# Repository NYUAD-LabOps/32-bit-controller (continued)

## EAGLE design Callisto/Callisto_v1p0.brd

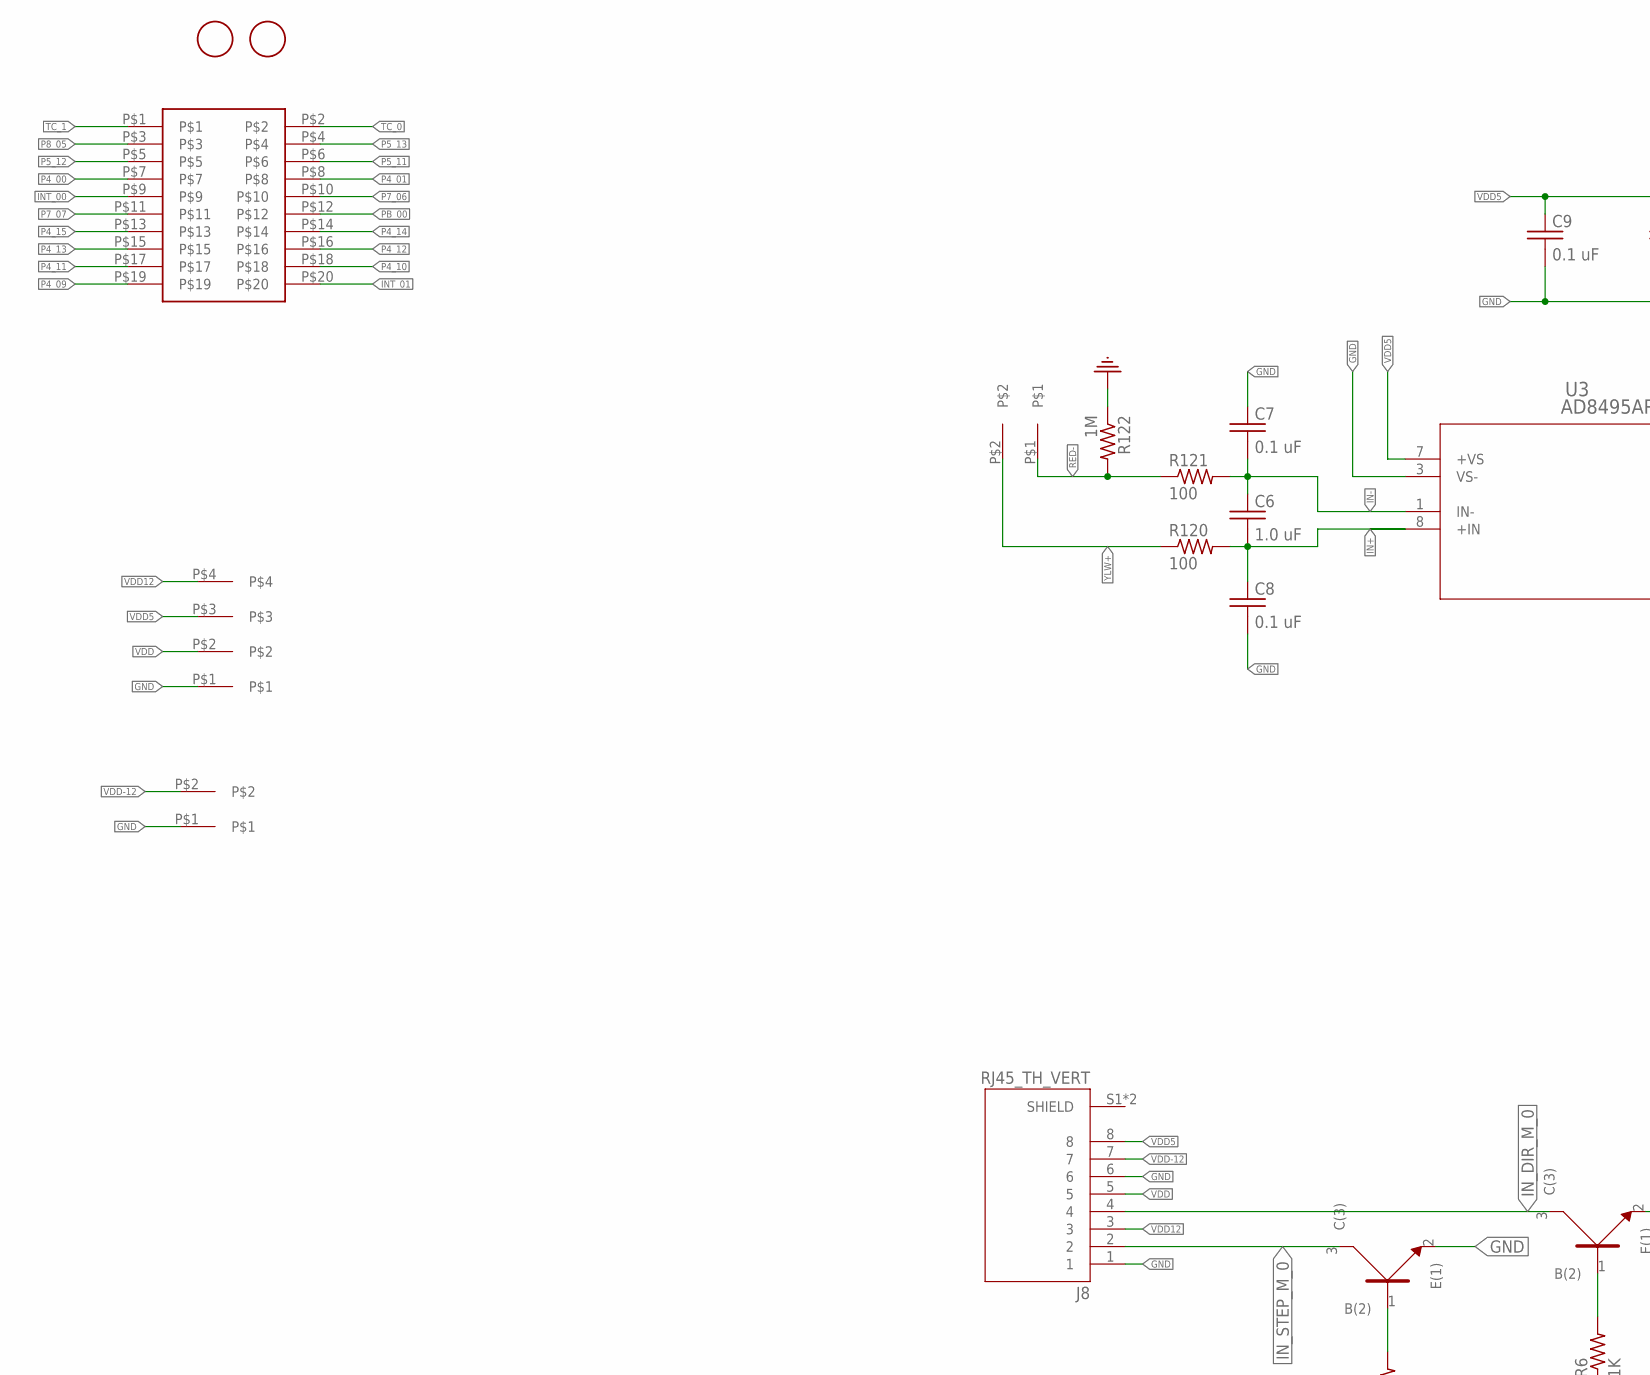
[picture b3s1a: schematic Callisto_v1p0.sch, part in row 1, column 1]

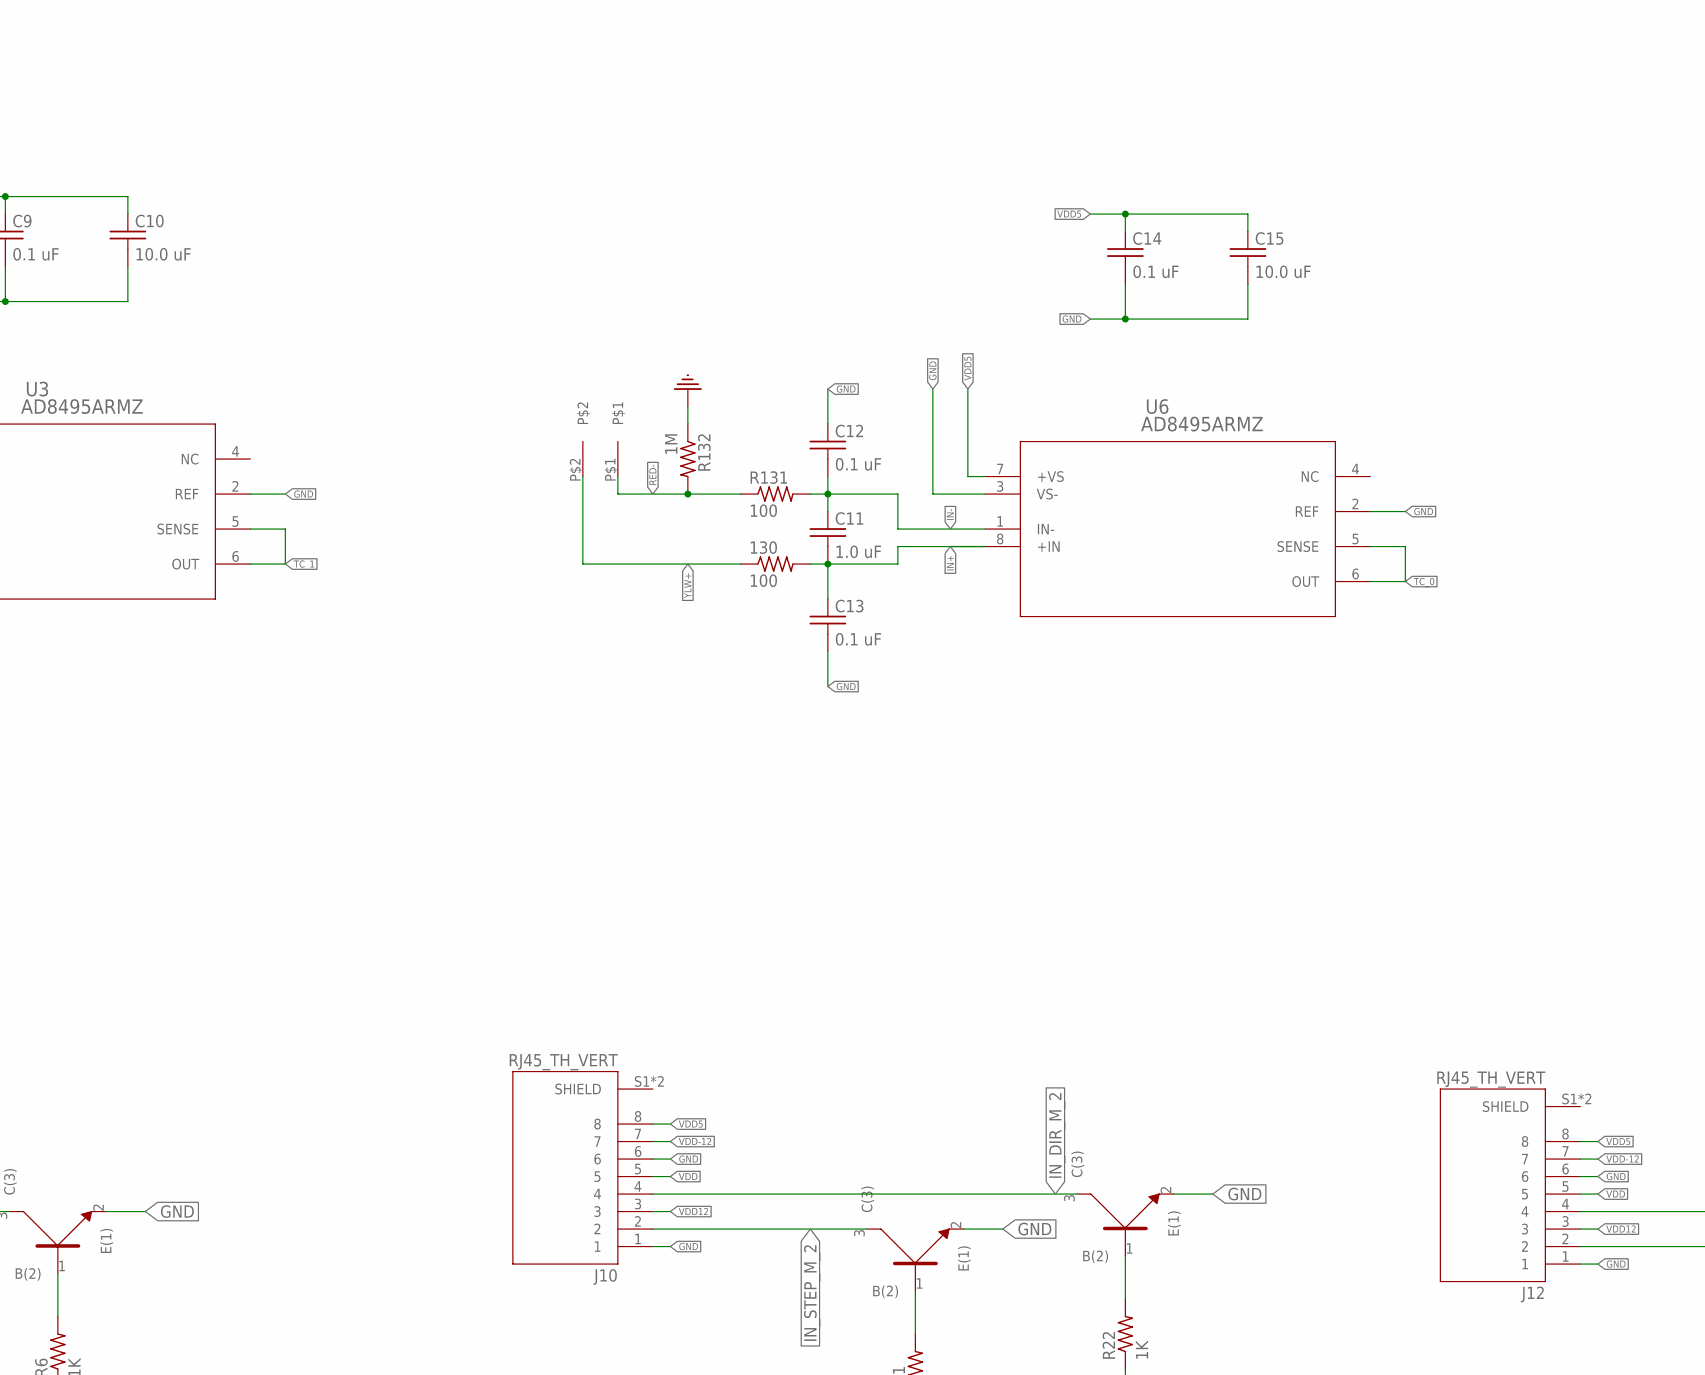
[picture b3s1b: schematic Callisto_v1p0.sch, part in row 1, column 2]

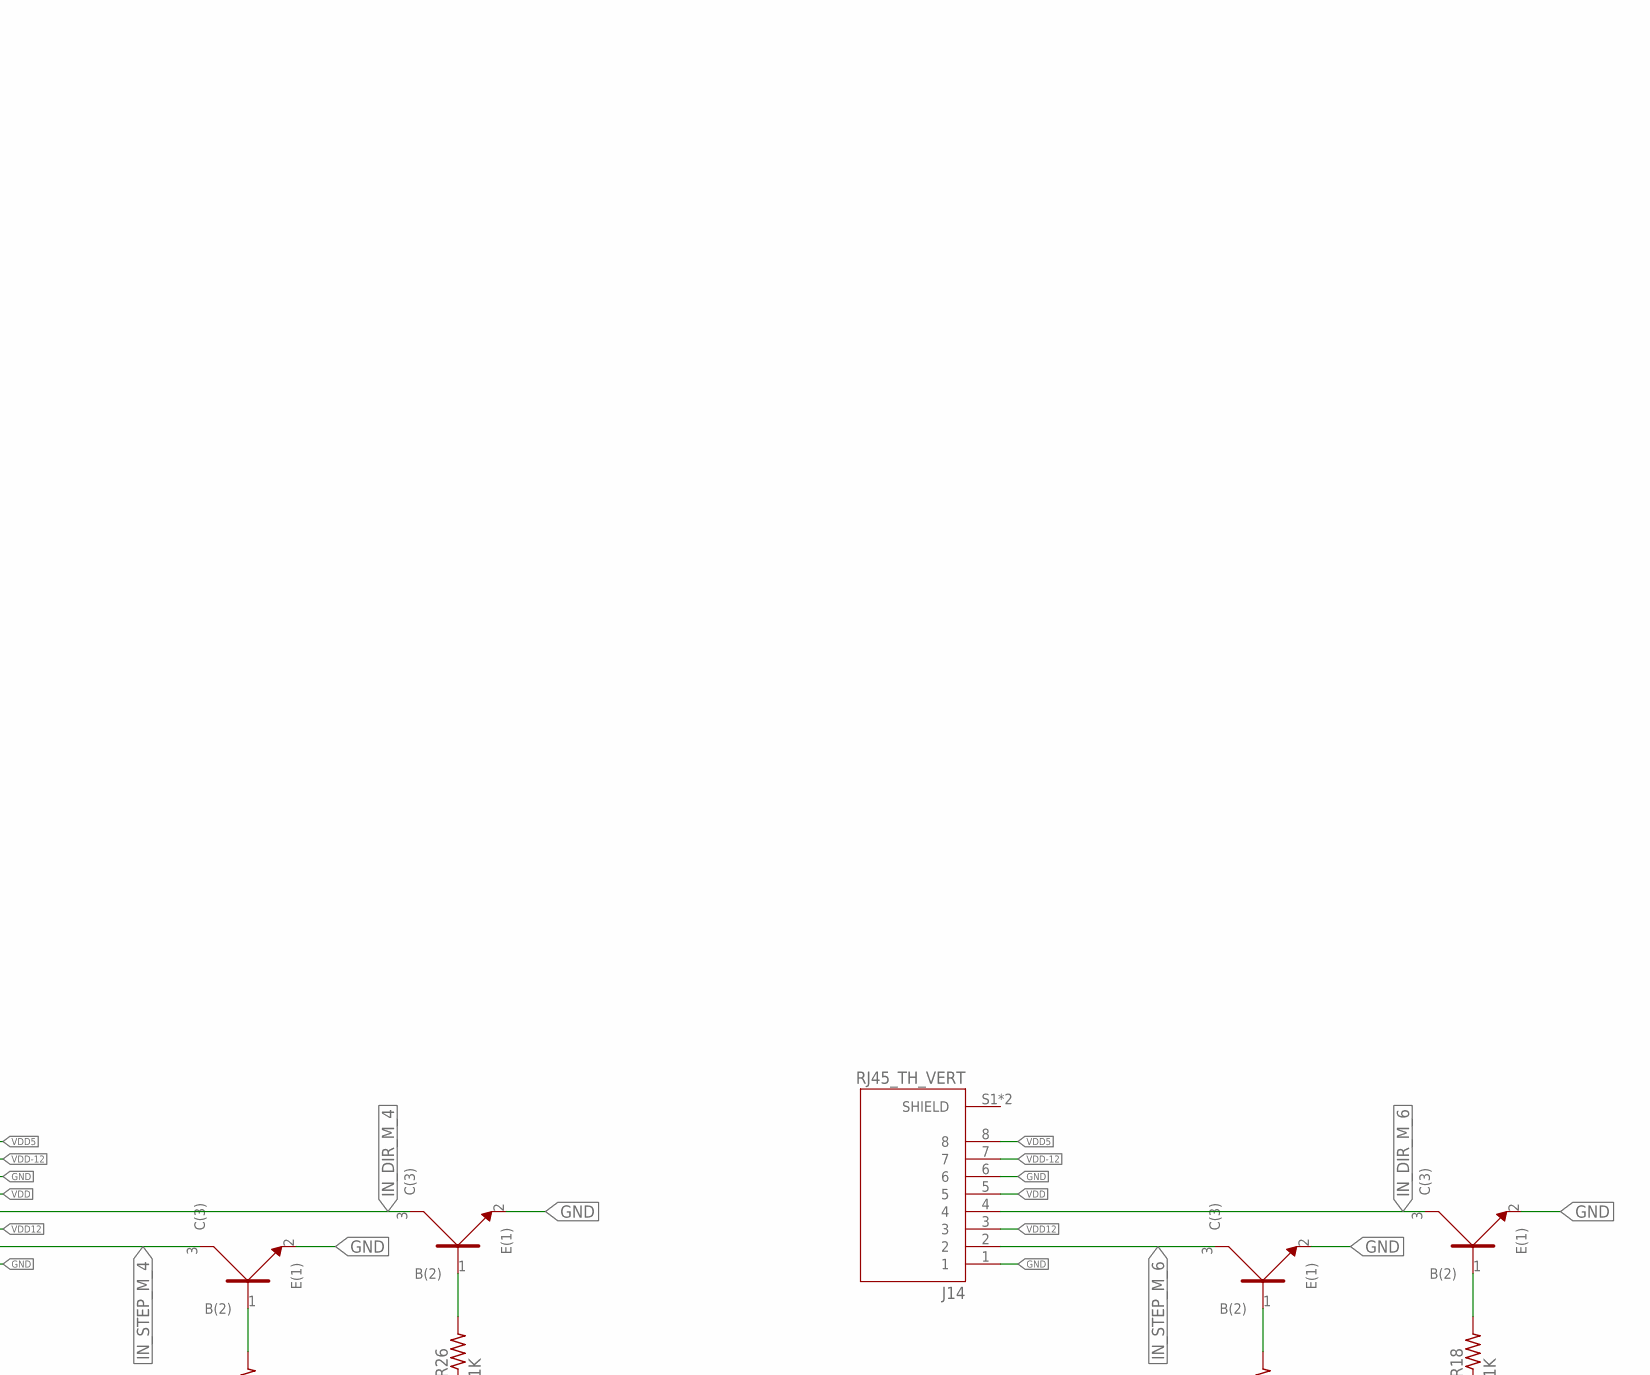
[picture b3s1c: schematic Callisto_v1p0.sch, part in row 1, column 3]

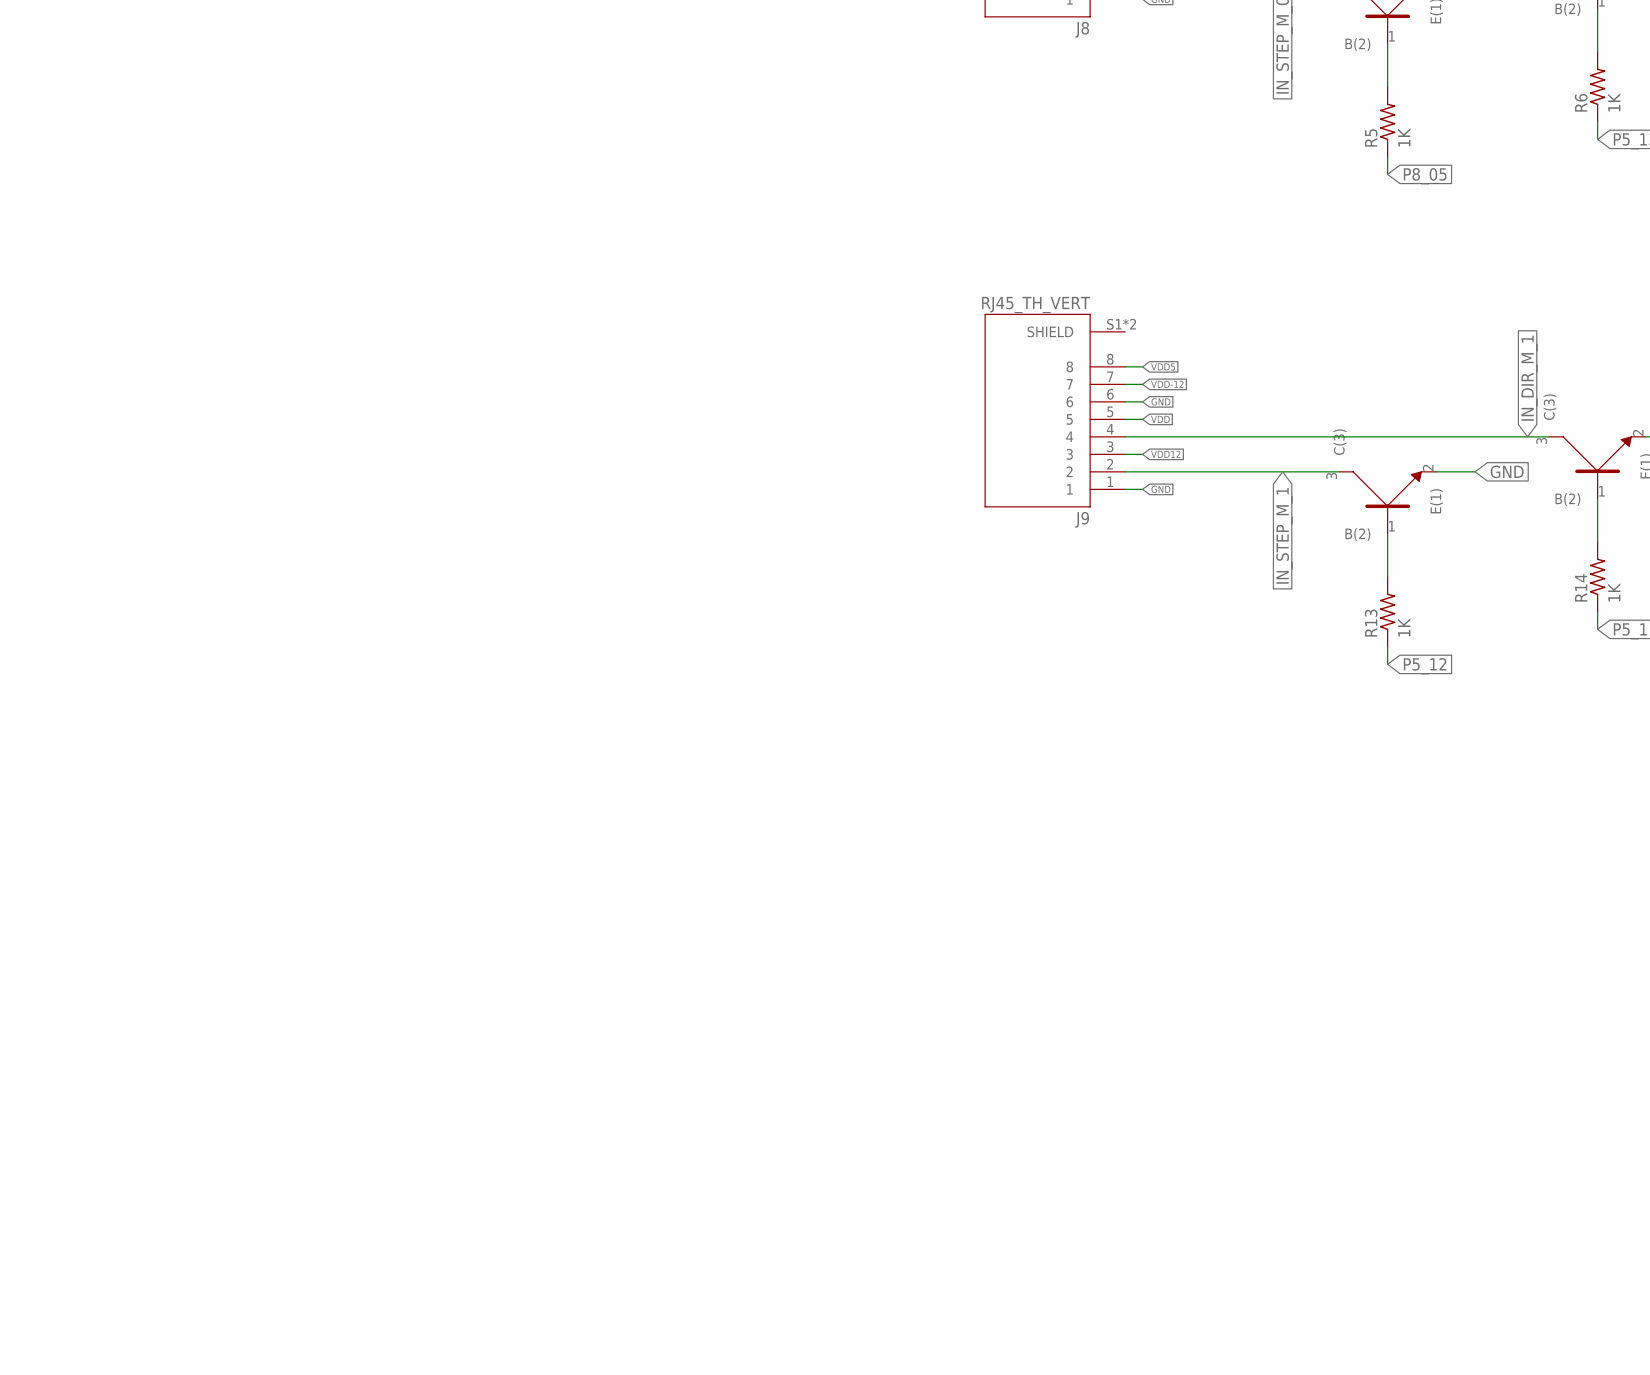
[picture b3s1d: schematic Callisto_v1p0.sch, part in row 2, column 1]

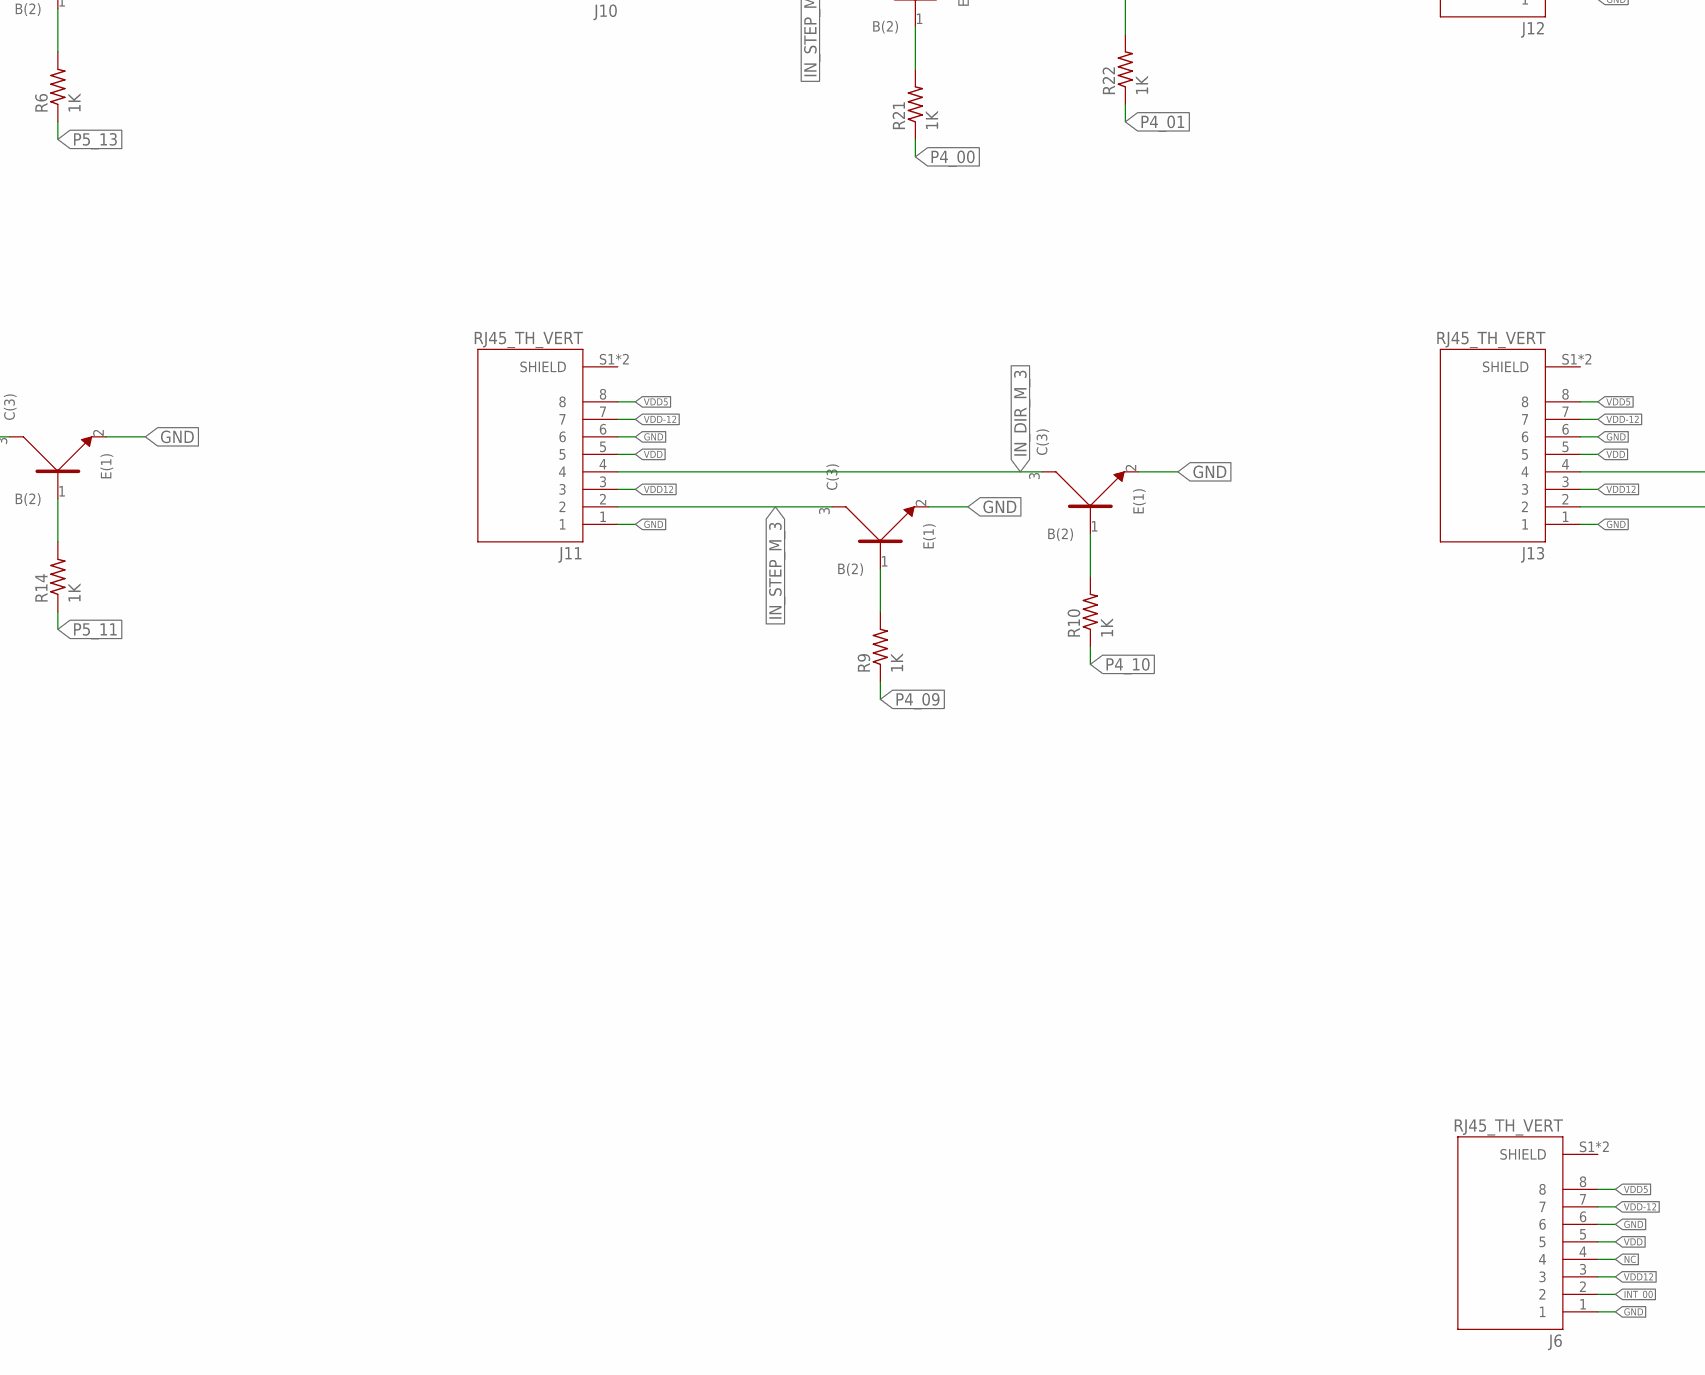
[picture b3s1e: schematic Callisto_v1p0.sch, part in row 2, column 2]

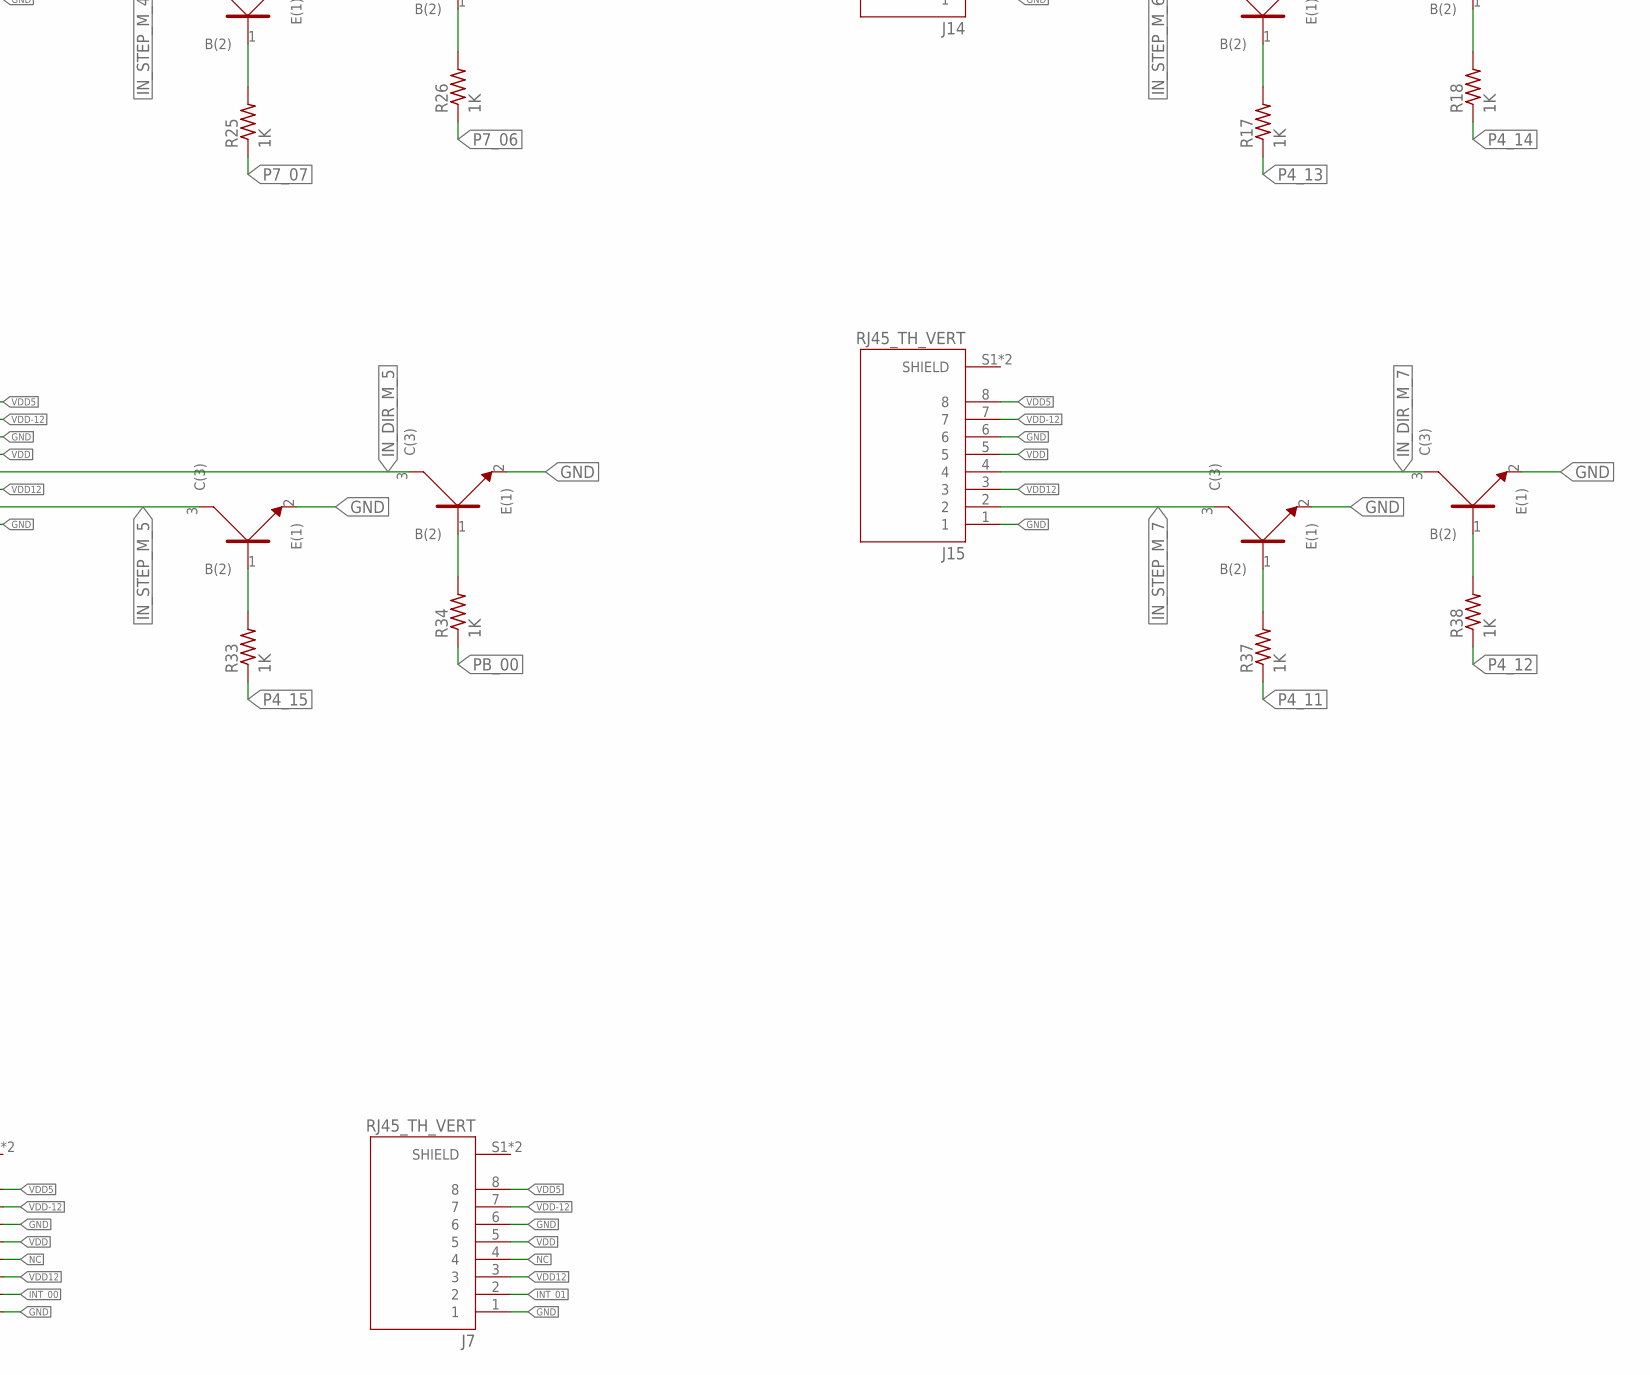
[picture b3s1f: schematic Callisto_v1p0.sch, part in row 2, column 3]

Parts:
130: 100; 0402
C6, C11: 1.0 uF; 0402
C7, C8, C9, C12, C13, C14: 0.1 uF; 0402
C10, C15: 10.0 uF; 0402
J1: 20-pos; 2_X_10_.1_INCH
J2, J3, J4: 2-pos; 2_3.81MM_PITCH
J5: 4-pos; 1X4_3.81MM_PITCH
J6, J7, J8, J9, J10, J11, J12, J13, J14, J15: RJ45_TH_VERT; ASSMANN_A-2014-2S-4-N-R
R5, R6, R9, R10, R13, R14, R17, R18, R21, R22, R25, R26, R33, R34, R37, R38: 1K; 0402
R120, R121, R131: 100; 0402
R122, R132: 1M; 0402
U1, U2, U4, U5, U7, U8, U9, U10, U11, U12, U13, U14, U17, U18, U19, U20: NPN; SOT323
U3, U6: AD8495ARMZ; RM_8_ADI
U$1, U$2: FIDUCIAL_1MM

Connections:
GND: C7.P$1 (1), C8.P$2 (2), C9.P$2 (2), C10.P$2 (2), C12.P$1 (1), C13.P$2 (2), C14.P$2 (2), C15.P$2 (2), J4.P$1, J5.P$1, J6.1, J6.6, J7.1, J7.6, J8.1, J8.6, J9.1, J9.6, J10.1, J10.6, J11.1, J11.6, J12.1, J12.6, J13.1, J13.6, J14.1, J14.6, J15.1, J15.6, R122.P$1 (1), R132.P$1 (1), U1.2 (E(1)), U2.2 (E(1)), U3.2 (REF), U3.3 (VS-), U4.2 (E(1)), U5.2 (E(1)), U6.2 (REF), U6.3 (VS-), U7.2 (E(1)), U8.2 (E(1)), U9.2 (E(1)), U10.2 (E(1)), U11.2 (E(1)), U12.2 (E(1)), U13.2 (E(1)), U14.2 (E(1)), U17.2 (E(1)), U18.2 (E(1)), U19.2 (E(1)), U20.2 (E(1))
IN+: 130.P$2 (2), C6.P$2 (2), C8.P$1 (1), C11.P$2 (2), C13.P$1 (1), R120.P$2 (2), U3.8 (+IN), U6.8 (+IN)
IN-: C6.P$1 (1), C7.P$2 (2), C11.P$1 (1), C12.P$2 (2), R121.P$2 (2), R131.P$2 (2), U3.1 (IN-), U6.1 (IN-)
INT_00: J1.P$9, J6.2
INT_01: J1.P$20, J7.2
IN_DIR_M_0: J8.4, U2.3 (C(3))
IN_DIR_M_1: J9.4, U8.3 (C(3))
IN_DIR_M_2: J10.4, U12.3 (C(3))
IN_DIR_M_3: J11.4, U5.3 (C(3))
IN_DIR_M_4: J12.4, U14.3 (C(3))
IN_DIR_M_5: J13.4, U18.3 (C(3))
IN_DIR_M_6: J14.4, U10.3 (C(3))
IN_DIR_M_7: J15.4, U20.3 (C(3))
IN_STEP_M_0: J8.2, U1.3 (C(3))
IN_STEP_M_1: J9.2, U7.3 (C(3))
IN_STEP_M_2: J10.2, U11.3 (C(3))
IN_STEP_M_3: J11.2, U4.3 (C(3))
IN_STEP_M_4: J12.2, U13.3 (C(3))
IN_STEP_M_5: J13.2, U17.3 (C(3))
IN_STEP_M_6: J14.2, U9.3 (C(3))
IN_STEP_M_7: J15.2, U19.3 (C(3))
unnamed: R5.P$2 (2), U1.1 (B(2))
unnamed: R6.P$2 (2), U2.1 (B(2))
unnamed: R9.P$2 (2), U4.1 (B(2))
unnamed: R10.P$2 (2), U5.1 (B(2))
unnamed: R13.P$2 (2), U7.1 (B(2))
unnamed: R14.P$2 (2), U8.1 (B(2))
unnamed: R17.P$2 (2), U9.1 (B(2))
unnamed: R18.P$2 (2), U10.1 (B(2))
unnamed: R21.P$2 (2), U11.1 (B(2))
unnamed: R22.P$2 (2), U12.1 (B(2))
unnamed: R25.P$2 (2), U13.1 (B(2))
unnamed: R26.P$2 (2), U14.1 (B(2))
unnamed: R33.P$2 (2), U17.1 (B(2))
unnamed: R34.P$2 (2), U18.1 (B(2))
unnamed: R37.P$2 (2), U19.1 (B(2))
unnamed: R38.P$2 (2), U20.1 (B(2))
NC: J6.4, J7.4
P4_00: J1.P$7, R21.P$1 (1)
P4_01: J1.P$8, R22.P$1 (1)
P4_09: J1.P$19, R9.P$1 (1)
P4_10: J1.P$18, R10.P$1 (1)
P4_11: J1.P$17, R37.P$1 (1)
P4_12: J1.P$16, R38.P$1 (1)
P4_13: J1.P$15, R17.P$1 (1)
P4_14: J1.P$14, R18.P$1 (1)
P4_15: J1.P$13, R33.P$1 (1)
P5_11: J1.P$6, R14.P$1 (1)
P5_12: J1.P$5, R13.P$1 (1)
P5_13: J1.P$4, R6.P$1 (1)
P7_06: J1.P$10, R26.P$1 (1)
P7_07: J1.P$11, R25.P$1 (1)
P8_05: J1.P$3, R5.P$1 (1)
PB_00: J1.P$12, R34.P$1 (1)
RED-: J2.P$1, J3.P$1, R121.P$1 (1), R122.P$2 (2), R131.P$1 (1), R132.P$2 (2)
TC_0: J1.P$2, U6.5 (SENSE), U6.6 (OUT)
TC_1: J1.P$1, U3.5 (SENSE), U3.6 (OUT)
VDD: J5.P$2, J6.5, J7.5, J8.5, J9.5, J10.5, J11.5, J12.5, J13.5, J14.5, J15.5
VDD5: C9.P$1 (1), C10.P$1 (1), C14.P$1 (1), C15.P$1 (1), J5.P$3, J6.8, J7.8, J8.8, J9.8, J10.8, J11.8, J12.8, J13.8, J14.8, J15.8, U3.7 (+VS), U6.7 (+VS)
VDD12: J5.P$4, J6.3, J7.3, J8.3, J9.3, J10.3, J11.3, J12.3, J13.3, J14.3, J15.3
VDD-12: J4.P$2, J6.7, J7.7, J8.7, J9.7, J10.7, J11.7, J12.7, J13.7, J14.7, J15.7
YLW+: 130.P$1 (1), J2.P$2, J3.P$2, R120.P$1 (1)

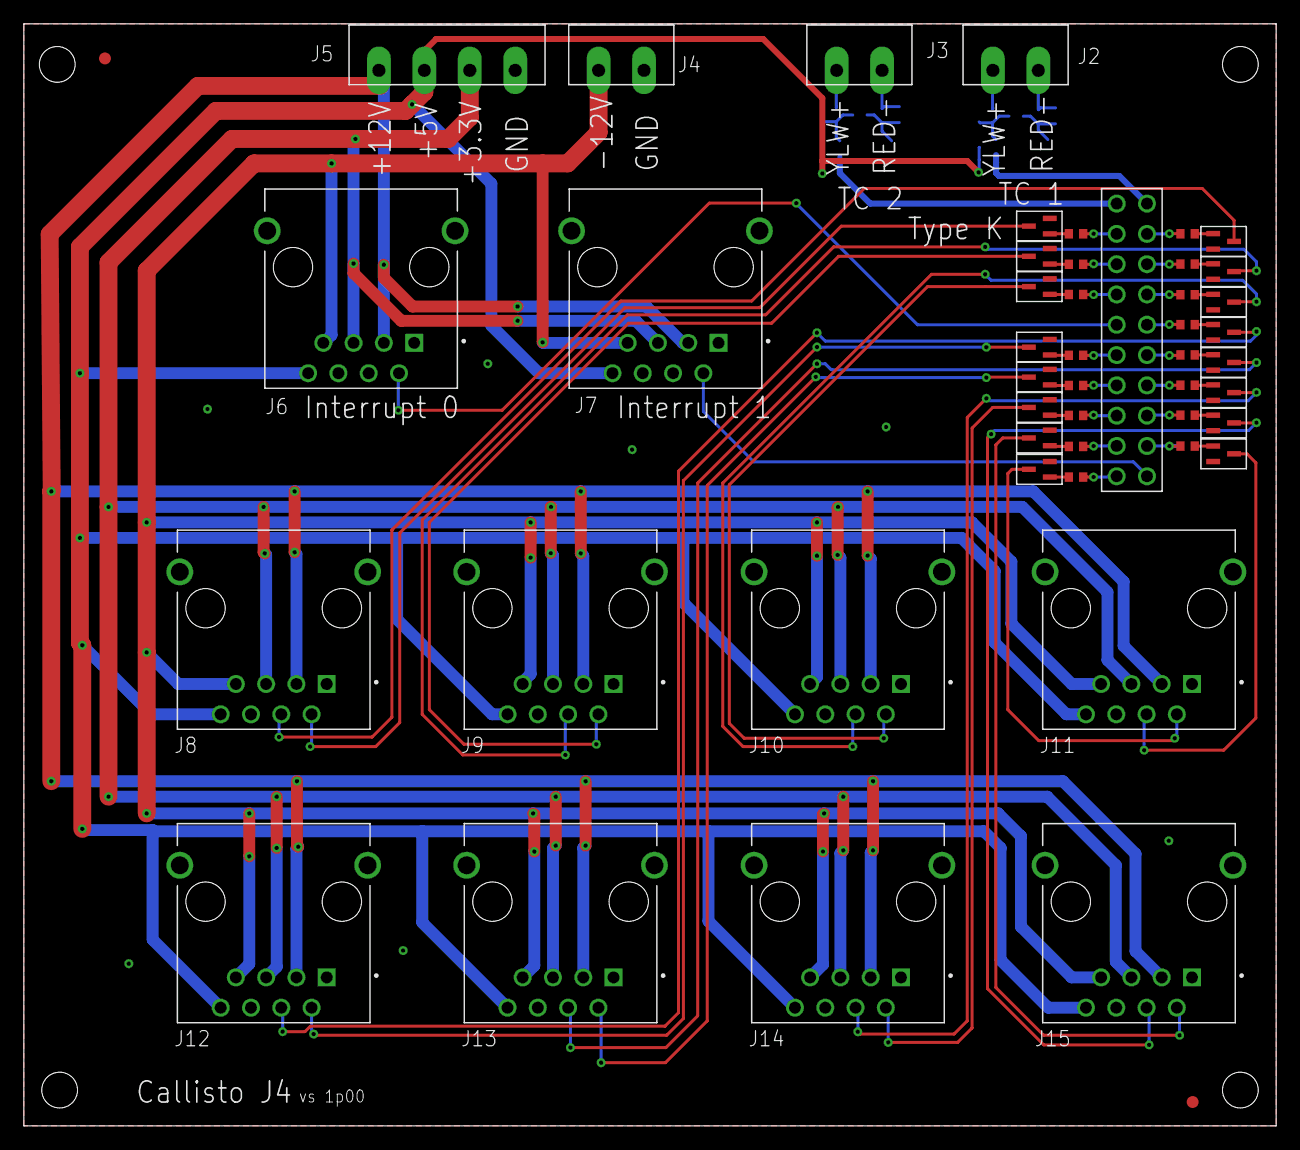
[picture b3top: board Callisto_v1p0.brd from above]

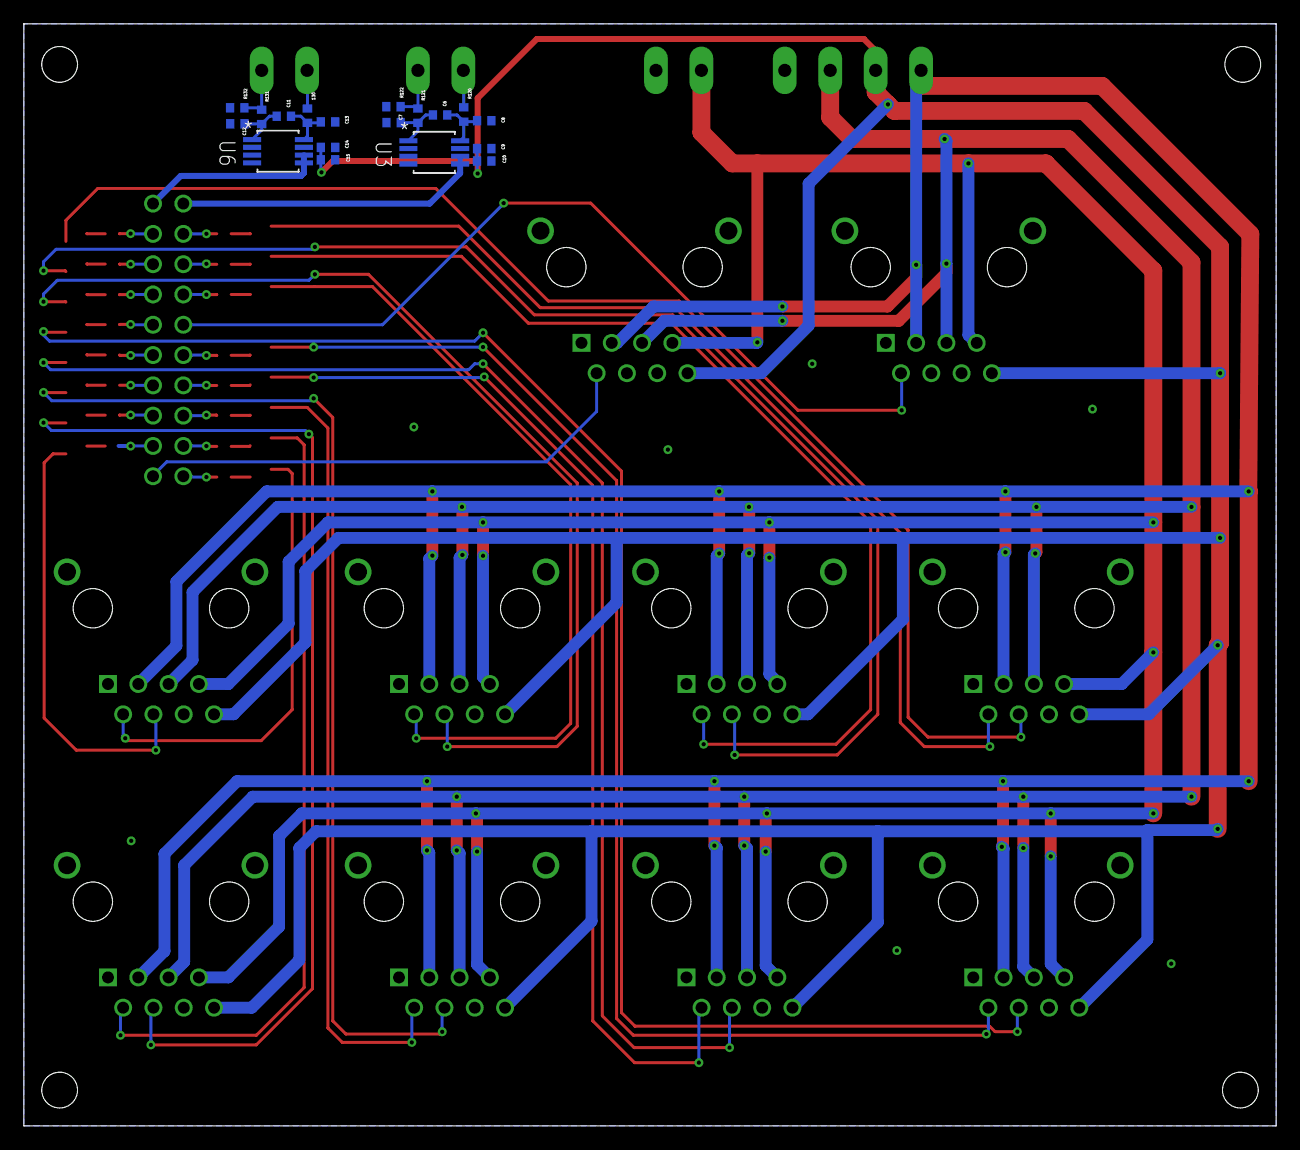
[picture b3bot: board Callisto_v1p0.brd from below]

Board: 2 copper layers, 105.0 x 92.4 mm, 67 parts (18 on the bottom side), 62 nets.
